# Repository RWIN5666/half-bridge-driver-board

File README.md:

# Tiny Half-Bridge Driver Board

This board has been designed to provide an easy way to add a MOSFET driver with a small footprint to a system. There is no mounting holes but the board can glued (kapton tape applied on the board bottom is recommended !!!).

Although it does not provide as good performance as a board that contains these components with an optimal PCB layout, it can work great. 

## WARNING !

I cannot be held responsible for anything that can happen using this design. 

## Made With Kicad

This board has been designed using [Kicad](http://kicad-pcb.org/) EDA and Kicad default component libraries (symbols, footprints and 3D models).

## Contributing

Feel free to download and improve the design.

## Authors
* **RWIN5666** - [Github Repos](https://github.com/RWIN5666)

See also the list of [contributors](https://github.com/RWIN5666/Poll-Filler/graphs/contributors) who participated in this project.

## License

I'm thinking about licensing the project... But I don't know which one yet. Feel free to make a pull request to suggest a license.

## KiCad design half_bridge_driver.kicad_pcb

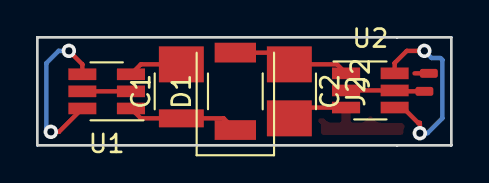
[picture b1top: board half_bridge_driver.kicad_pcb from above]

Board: 2 copper layers, 23.0 x 6.0 mm, 7 parts (0 on the bottom side), 8 nets.

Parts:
C1, C2: 10µF; C_1210
D1: GB01SLT12-214; D_SMB
J2, J2#2: Conn_01x01_Male; SolderWirePad_single_SMD_5x10mm
U1, U2: ZXGD3003E6; SOT-23-6_Handsoldering

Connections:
+15V: C2.1, D1.2, U2.1
/15V_High_Side: C1.1, D1.1, U1.1
/GND_High_Side: C1.2, U1.3
/High_Side_Input: U1.2, U1.5
/High_Side_MOSFET_Gate: U1.4, U1.6
/Low_Side_Input: J2#2.1, U2.2, U2.5
/Low_Side_MOSFET_Gate: U2.4, U2.6
GND: C2.2, U2.3

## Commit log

2018-07-27 Initial commit.
2018-07-30 Fixed high driver orientation and added one pad for external wiring.
2018-07-30 Added extra pad to test external wiring.
2018-08-03 Added extra pad for input and output driver signals to ease wire soldering.
2018-08-03 Added docs.
